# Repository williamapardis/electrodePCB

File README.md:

# electrodePCB
A convenient solution-circuit interface. The electrode printed circuit board (PCB) is a experimental utility with submersible application of electrochemistry in mind. The PCB is designed to fasten directly to a Blue Robotic (BR) Enclosure - [2" Cylindrical Locking Series - O-ring flanges](https://bluerobotics.com/store/watertight-enclosures/locking-series/wte-flange-vp/). The front side (or wet side) of the PCB is a layout of gold plated pads that act as substrate for unique solution processed electrode materials. The back side (or dry side) internal to the BR enclosure hosts both passive and active circuitry, their respective layout and interconnection to circuit and electrodes thought a multi. pos. FPC cable. 

## rE

We have upgraded to a 20 position FPC connector to accomidate more features. One these features include an additional heating element for thermal probing of the electrodes. Probing of the.

## rD

## rC

## rB

## rA

### next revision
add a convenient way to disconnect electrodes from FPC

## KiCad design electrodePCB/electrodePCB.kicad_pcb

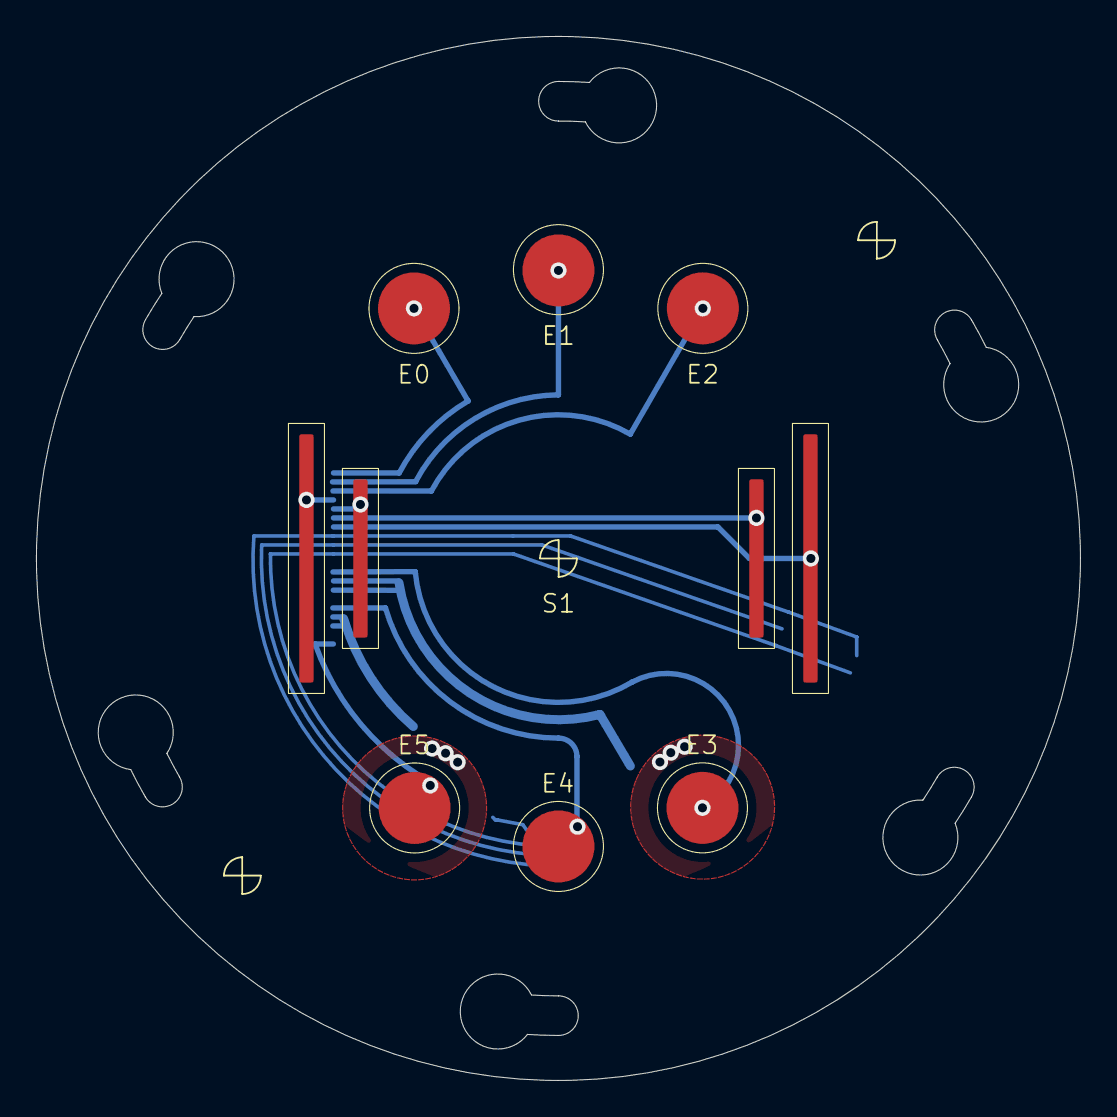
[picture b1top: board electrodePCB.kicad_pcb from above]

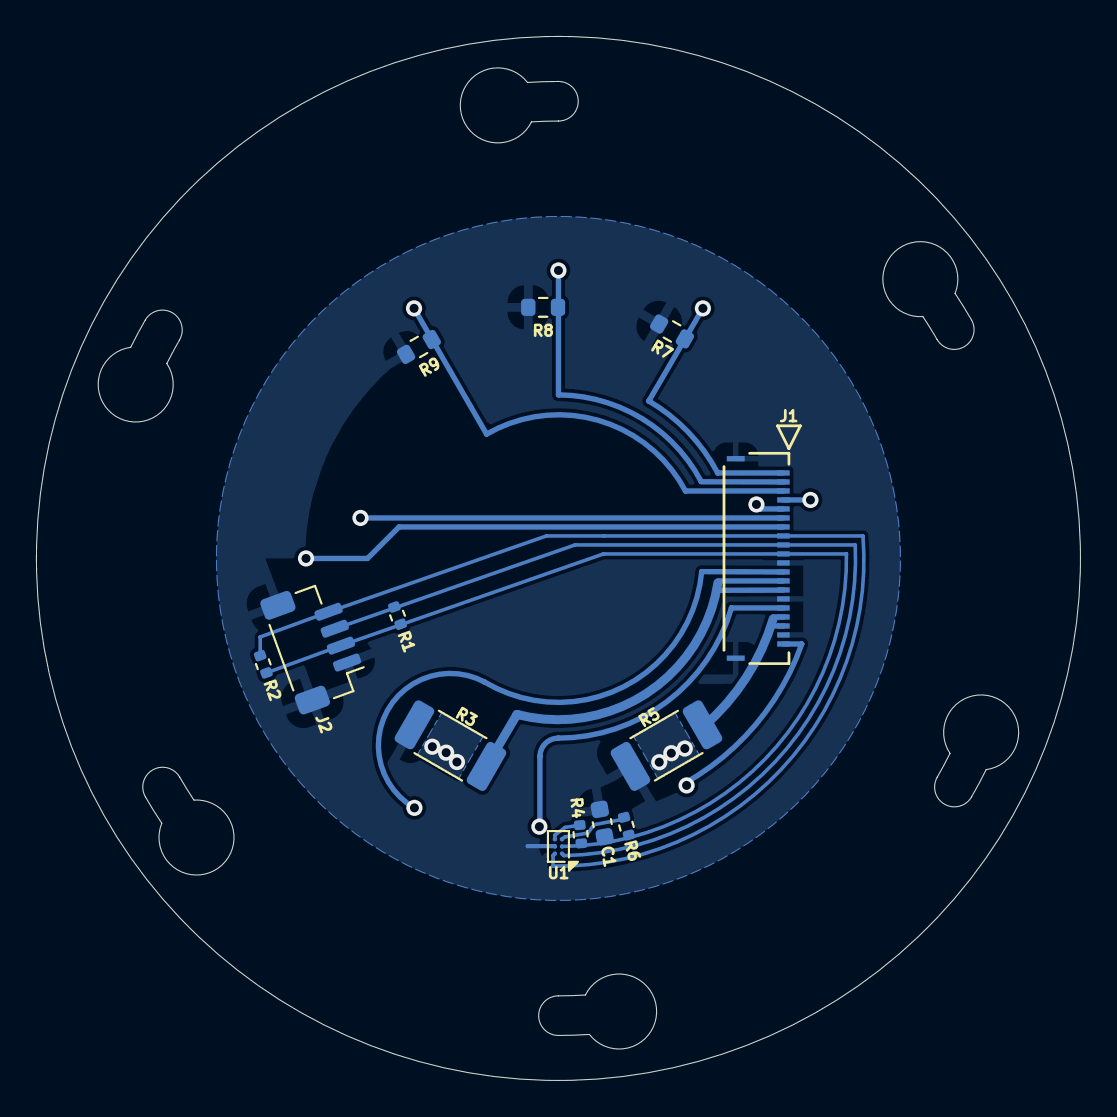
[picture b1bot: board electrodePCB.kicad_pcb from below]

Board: 2 copper layers, 58.0 x 58.0 mm, 20 parts (13 on the bottom side), 18 nets.

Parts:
C1: 0.1uF; C_0603_1608Metric
E0, E1, E2, E3, E4, E5: Conn_01x01; Circular_10mm
J1: FPC 20p; CON_5034802000_MOL
J2: qwiic; JST_SH_BM04B-SRSS-TB_1x04-1MP_P1.00mm_Vertical
R1, R2, R4, R6: 10k; R_0402_1005Metric
R3, R5: R_Small_US; R_2010_5025Metric
R7, R8, R9: R_US; R_0603_1608Metric
S1: 4E Conductivity Cell; Conductivity_Cell_K10
U1: TMP119AIYBGR; Texas_DSBGA-6_0.95x1.488mm_Layout2x3_P0.4mm

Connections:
+3V3: C1.1, J1.10, J2.2, R1.1, R2.2, R4.2, R6.1, U1.B1 (V+)
GND: C1.2, J1.11, J1.15, J1.19, J1.P1, J1.P2, J2.1, J2.MP (MountPin), R3.2, R5.2, R7.1, R8.1, R9.1, U1.B2 (GND)
unnamed: E0.1, J1.1, R7.2
unnamed: E1.1, J1.2, R8.2
unnamed: E2.1, J1.3, R9.2
unnamed: E3.1, J1.12
unnamed: E4.1, J1.16
unnamed: E5.1, J1.20
unnamed: J1.4, S1.1
unnamed: J1.5, S1.2
unnamed: J1.6, S1.3
unnamed: J1.7, S1.4
unnamed: J1.13, J1.14, R3.1
unnamed: J1.17, J1.18, R5.1
unnamed: R6.2, U1.C1 (ADD0)
unnamed: R4.1, U1.C2 (ALERT)
SCL: J1.8, J2.4, R2.1, U1.A2 (SCL)
SDA: J1.9, J2.3, R1.2, U1.A1 (SDA)

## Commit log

2026-05-06 adding KiCad design files and a seperate directory specifically for zip'd fab. files
2026-05-06 still in the middle of it, but added the 20p, 2 additional heaters (including adjustable postition) and begining to define pinout
2026-05-07 bunch of routing, adapted interconnect pinout to accomedate routing. Added GND plane.
2026-05-08 routing, routing, routing. We removed one of the three heaters and decided to displace the other two and route to rings around the electrodes. I verified the temperature sensor is work!
2026-05-08 routing and more routing. still working, but add thermal rings. added qwiic.
2026-05-08 roughly finalized layout. Might tidy up the GND plane with some keep outs
2026-05-08 adding layout images and schematic of current design (all pdfs)
2026-05-08 added releifs for screws so we do not have to completely remove them
2026-05-08 cleaning up GND plane and adapted thermal pads to have larger internal radius for fab flexibility.
2026-05-10 GND plane triming
2026-05-13 labeling of the Cond Cell
2026-05-22 generated cad file
2026-05-29 added holes to mask, increased via size for epoxy fill, created fabrication files output_rE
